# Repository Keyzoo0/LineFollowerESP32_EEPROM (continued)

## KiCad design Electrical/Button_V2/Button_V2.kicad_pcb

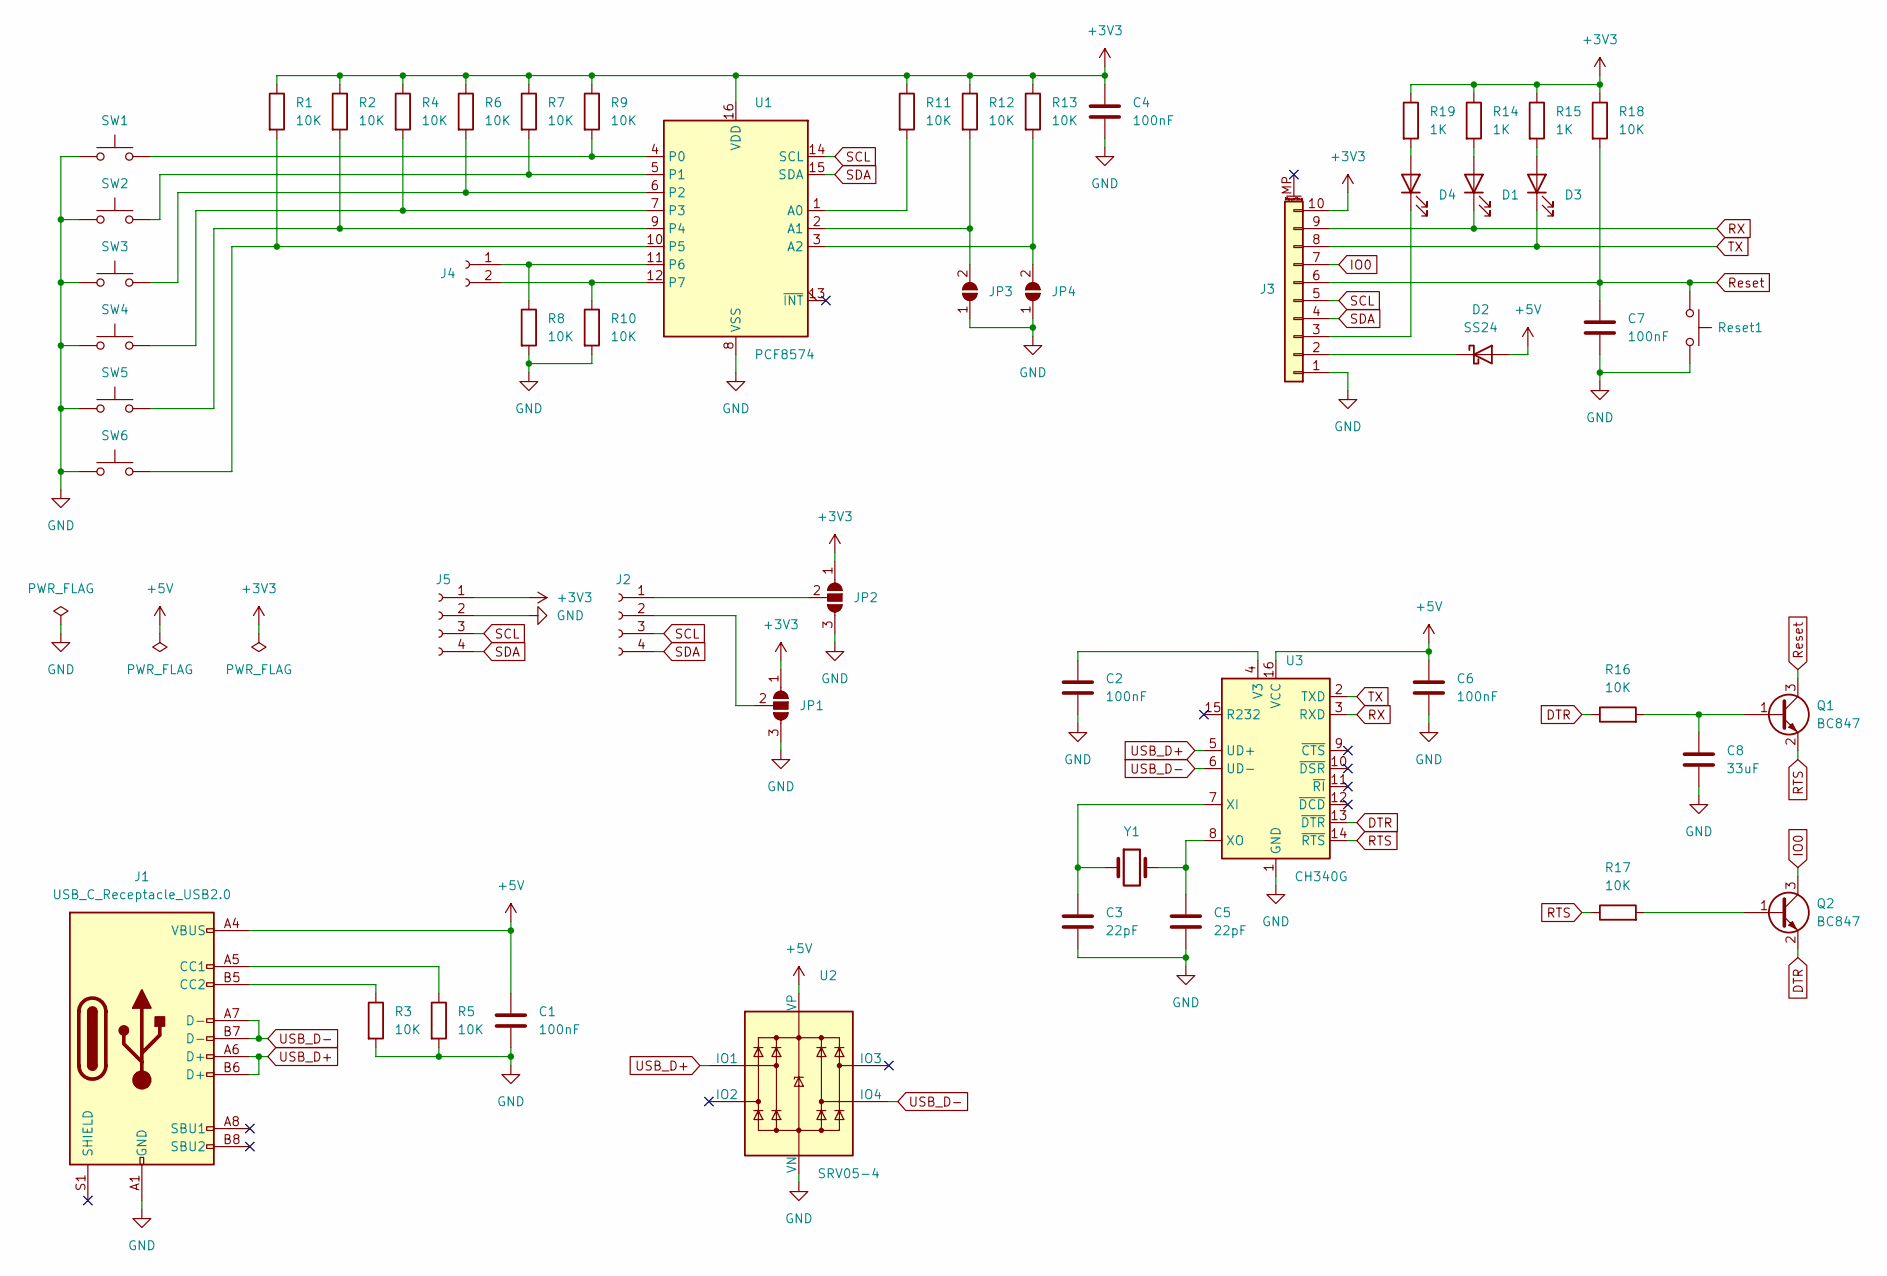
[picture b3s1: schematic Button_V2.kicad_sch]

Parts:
C1, C2, C4, C6, C7: 100nF; C_0805_2012Metric_Pad1.18x1.45mm_HandSolder
C3, C5: 22pF; C_0805_2012Metric_Pad1.18x1.45mm_HandSolder
C8: 33uF; C_0805_2012Metric_Pad1.18x1.45mm_HandSolder
D1, D3, D4: LED; LED_0805_2012Metric_Pad1.15x1.40mm_HandSolder
D2: SS24; DO_214
J1: USB_C_Receptacle_USB2.0; USB_C_Receptacle_HRO_TYPE-C-31-M-12
J2: Conn_01x04_Female; PinHeader_1x04_P2.54mm_Vertical
J3: Conn_01x10_MountingPin; TE_1-84952-0_1x10-1MP_P1.0mm_Horizontal
J4: Conn_01x02_Female; PinHeader_1x02_P2.54mm_Vertical
J5: Conn_01x04_Female
JP1, JP2: SolderJumper_3_Open; SolderJumper-3_P1.3mm_Open_RoundedPad1.0x1.5mm_NumberLabels
JP3, JP4: SolderJumper_2_Open; SolderJumper-2_P1.3mm_Open_TrianglePad1.0x1.5mm
Q1, Q2: BC847; SOT-23
R1, R2, R3, R4, R5, R6, R7, R8, R9, R10, R11, R12, R13, R16, R17, R18: 10K; R_0805_2012Metric_Pad1.20x1.40mm_HandSolder
R14, R15, R19: 1K; R_0805_2012Metric_Pad1.20x1.40mm_HandSolder
Reset1: SW_Push; Silent_Button
SW1, SW2, SW3, SW4, SW5, SW6: SW_Push; Silent_Button
U1: PCF8574; SOIC-16W_7.5x10.3mm_P1.27mm
U2: SRV05-4; SOT-23-6
U3: CH340G; SOIC-16_3.9x9.9mm_P1.27mm
Y1: Crystal; Crystal_SMD_HC49-SD

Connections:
+3V3: C4.1, J3.10, J5.1, JP1.1 (A), JP2.1 (A), R1.1, R2.1, R4.1, R6.1, R7.1, R9.1, R11.1, R12.1, R13.1, R14.1, R15.1, R18.1, R19.1, U1.16 (VDD)
+5V: C1.1, C6.1, D2.2 (A), J1.A4 (VBUS), J1.A9 (VBUS), J1.B4 (VBUS), J1.B9 (VBUS), U2.5 (VP), U3.16 (VCC)
DTR: Q2.2 (E), R16.1, U3.13 (~DTR)
GND: C1.2, C2.2, C3.2, C4.2, C5.2, C6.2, C7.2, C8.2, J1.A1 (GND), J1.A12 (GND), J1.B1 (GND), J1.B12 (GND), J3.1, J5.2, JP1.3 (B), JP2.3 (B), JP3.1 (A), JP4.1 (A), R3.2, R5.2, R8.2, R10.2, Reset1.2, SW1.1, SW2.1, SW3.1, SW4.1, SW5.1, SW6.1, U1.8 (VSS), U2.2 (VN), U3.1 (GND)
IO0: J3.7, Q2.3 (C)
unnamed: C2.1, U3.4 (V3)
unnamed: C3.1, U3.7 (XI), Y1.1
unnamed: C5.1, U3.8 (XO), Y1.2
unnamed: C8.1, Q1.1 (B), R16.2
unnamed: D1.2 (A), R14.2
unnamed: D2.1 (K), J3.2
unnamed: D3.2 (A), R15.2
unnamed: D4.1 (K), J3.3
unnamed: D4.2 (A), R19.2
unnamed: J1.A5 (CC1), R5.1
unnamed: J1.B5 (CC2), R3.1
unnamed: J2.1, JP2.2 (C)
unnamed: J2.2, JP1.2 (C)
unnamed: J4.1, R8.1, U1.11 (P6)
unnamed: J4.2, R10.1, U1.12 (P7)
unnamed: JP3.2 (B), R12.2, U1.2 (A1)
unnamed: JP4.2 (B), R13.2, U1.3 (A2)
unnamed: Q2.1 (B), R17.2
unnamed: R1.2, SW6.2, U1.10 (P5)
unnamed: R2.2, SW5.2, U1.9 (P4)
unnamed: R4.2, SW4.2, U1.7 (P3)
unnamed: R6.2, SW3.2, U1.6 (P2)
unnamed: R7.2, SW2.2, U1.5 (P1)
unnamed: R9.2, SW1.2, U1.4 (P0)
unnamed: R11.2, U1.1 (A0)
RTS: Q1.2 (E), R17.1, U3.14 (~RTS)
RX: D1.1 (K), J3.9, U3.3 (RXD)
Reset: C7.1, J3.6, Q1.3 (C), R18.2, Reset1.1
SCL: J2.3, J3.5, J5.3, U1.14 (SCL)
SDA: J2.4, J3.4, J5.4, U1.15 (SDA)
TX: D3.1 (K), J3.8, U3.2 (TXD)
USB_D+: J1.A6 (D+), J1.B6 (D+), U2.1 (IO1), U3.5 (UD+)
USB_D-: J1.A7 (D-), J1.B7 (D-), U2.6 (IO4), U3.6 (UD-)

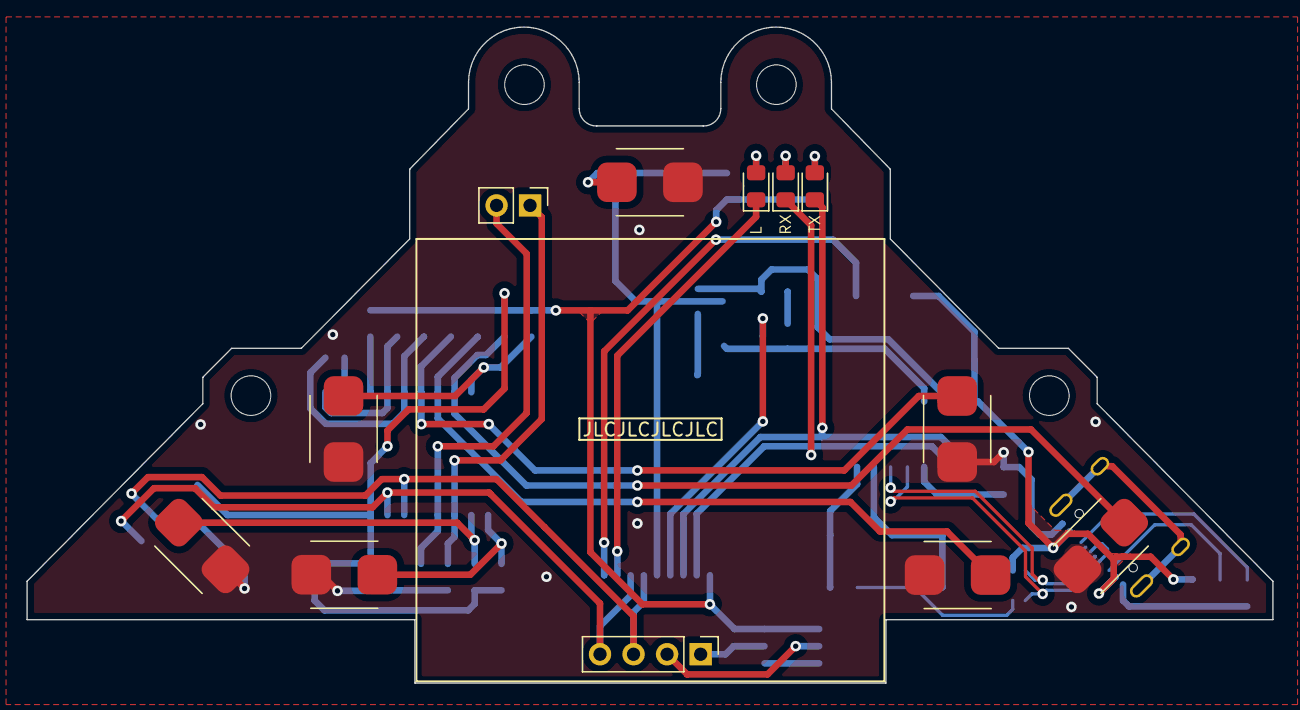
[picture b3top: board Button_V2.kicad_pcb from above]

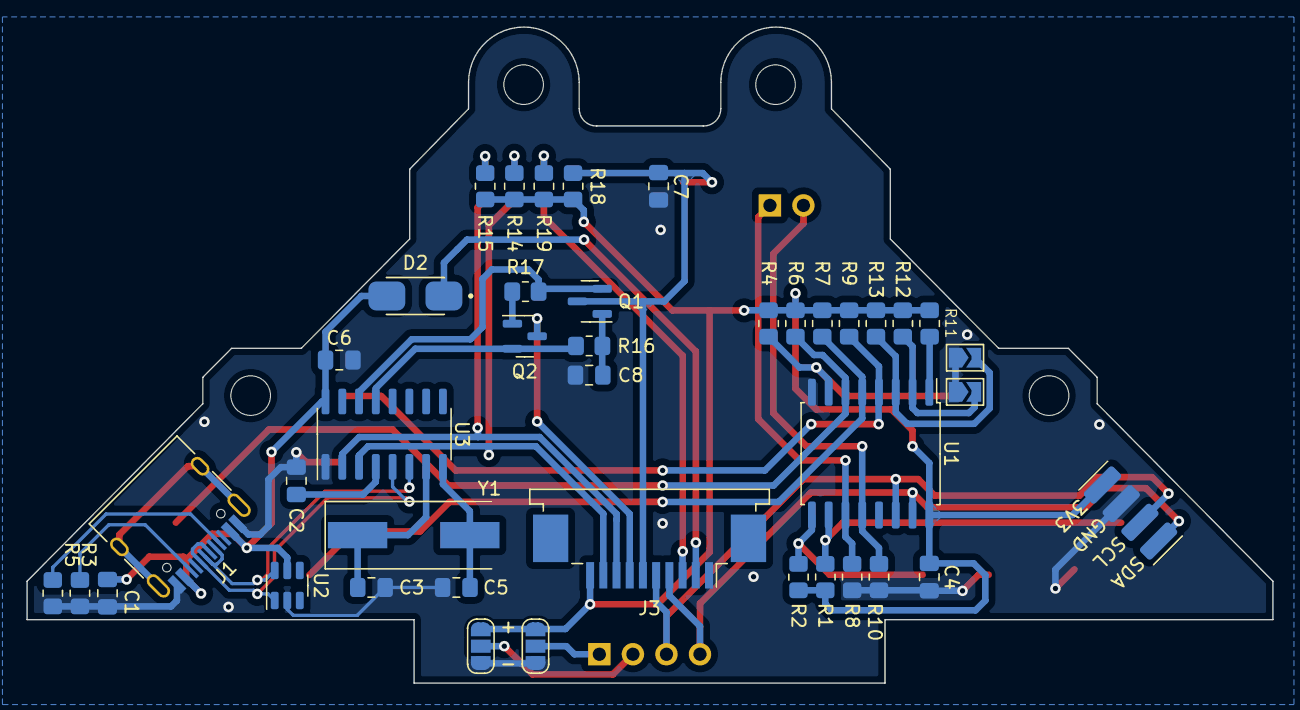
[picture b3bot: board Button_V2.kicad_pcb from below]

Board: 2 copper layers, 94.3 x 49.7 mm, 57 parts (41 on the bottom side), 38 nets.

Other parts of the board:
H1, H2, H2#2, H2#3: MountingHole; MountingHole_3mm

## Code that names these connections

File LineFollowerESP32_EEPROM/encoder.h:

#define ENC1A 33
#define ENC1B 25
#define ENC2A 39
#define ENC2B 36

int16_t countEnc_A;
int16_t countEnc_B;
int16_t rpmR, rpmL;
int16_t pulseL;
int16_t pulseR;
unsigned long lastTimeRPM;

#define CPR 208
#define DiameterRoda 17 // satuan mm
float factor = (PI * DiameterRoda) / (CPR);

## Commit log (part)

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2024-08-07 Fix Sensor Bug with kalman filter
    - fix the PID
2024-08-08 fix gui
